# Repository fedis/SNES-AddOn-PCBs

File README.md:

SNES-AddOn-PCBs
===============

Several PCBs for SNES for Different Purposes

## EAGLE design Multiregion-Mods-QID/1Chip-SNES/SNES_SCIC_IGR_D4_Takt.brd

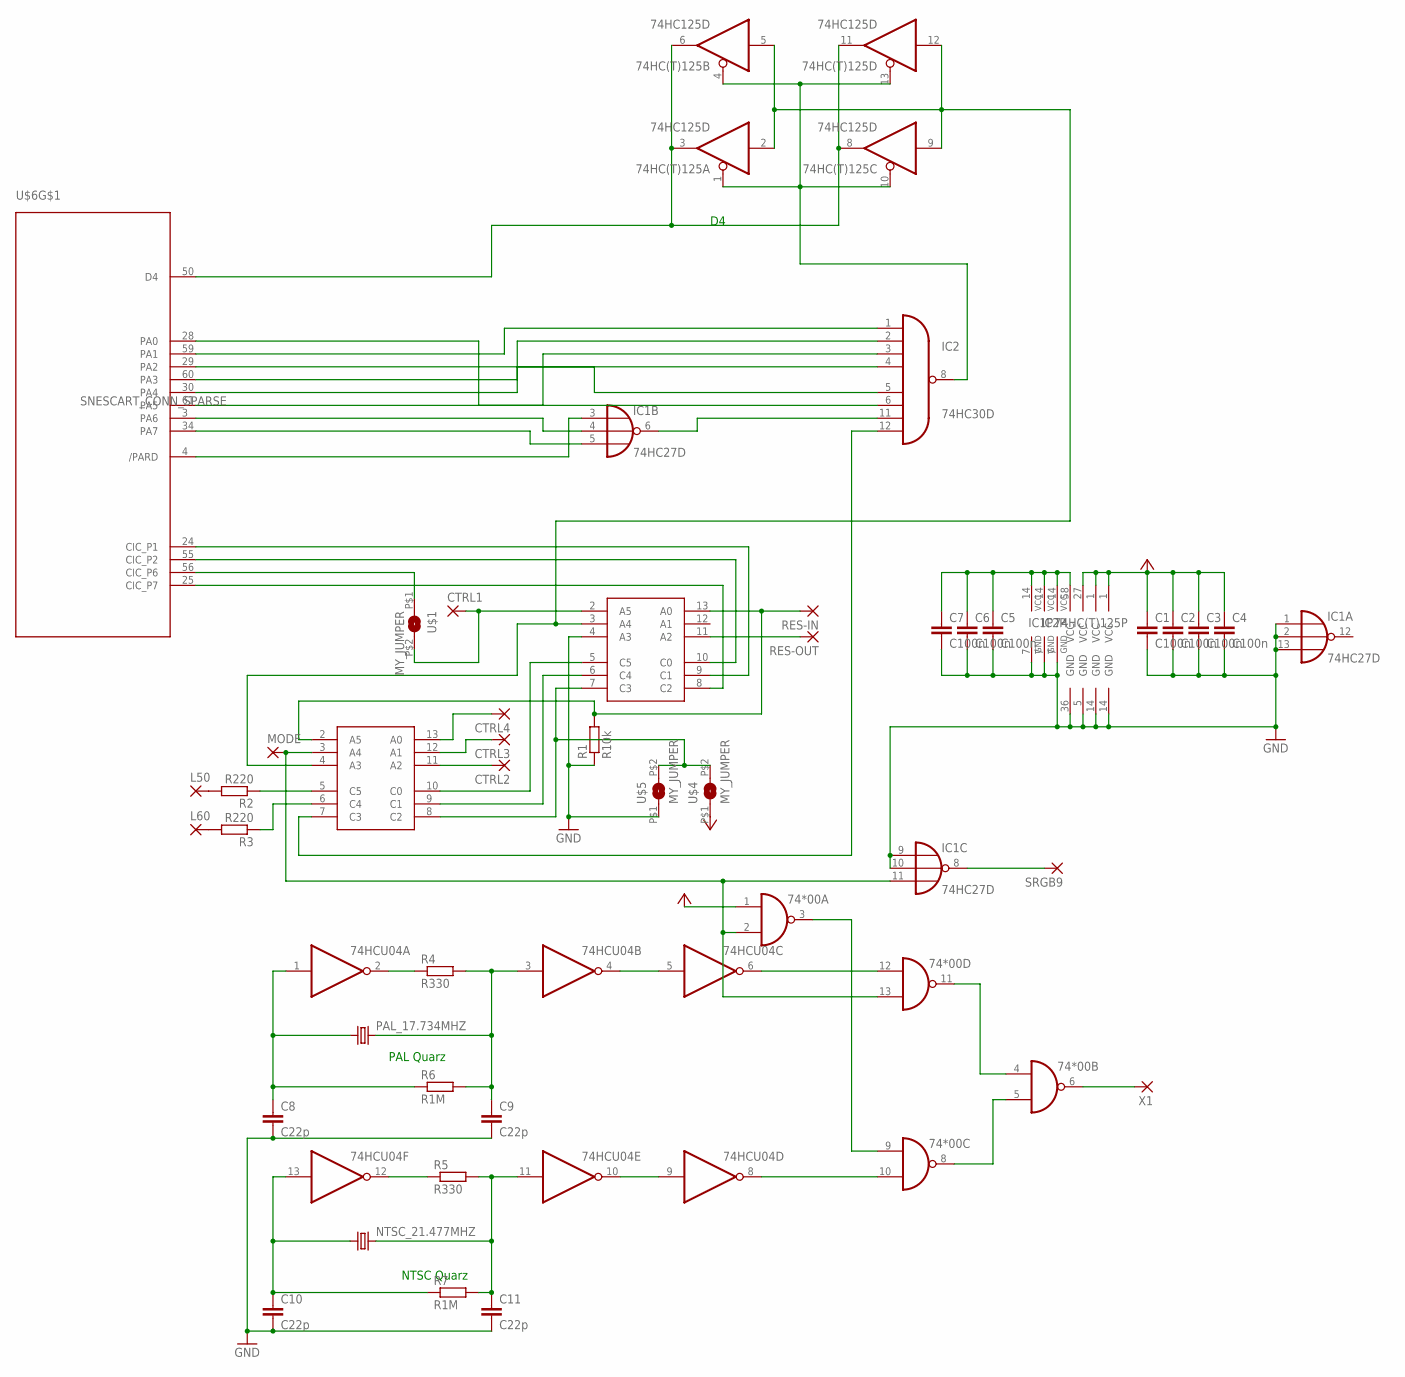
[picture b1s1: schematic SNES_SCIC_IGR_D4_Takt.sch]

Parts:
74*00: 7400D; SO14
74HC(T)125: 74HC125D; SO14
74HCU04: 74HC04D; SO14
C1, C2, C3, C4, C5, C6, C7: C100n; Z0805
C8, C9, C10, C11: C22p; Z0805
CTRL1, CTRL2, CTRL3, CTRL4: SMD2; SMD1,27-2,54
IC1: 74HC27D; SO14
IC2: 74HC30D; SO14
L50, L60: SMD2; SMD1,27-2,54
MODE: SMD2; SMD1,27-2,54
NTSC_21.477MHZ: CRYSTALHC49UP; HC49UP
PAL_17.734MHZ: CRYSTALHC49UP; HC49UP
R1: R10k; Z0805
R2, R3: R220; Z0805
R4, R5: R330; Z0805
R6, R7: R1M; Z0805
RES-IN: SMD2; SMD1,27-2,54
RES-OUT: SMD2; SMD1,27-2,54
SRGB9: SMD2; SMD1,27-2,54
U$1, U$4, U$5: MY_JUMPER; MYJUMP
U$2, U$3: PIC16F630_SIMPLE; PIC16F630
U$6: SNESCART_CONN_SPARSE
X1: SMD2; SMD1,27-2,54

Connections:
GND: 74*00.7 (GND), 74HC(T)125.7 (GND), 74HCU04.7 (GND), C1.2, C2.2, C3.2, C4.2, C5.2, C6.2, C7.2, C8.2, C9.2, C10.2, C11.2, IC1.1 (I0), IC1.2 (I1), IC1.7 (GND), IC1.9 (I0), IC1.10 (I1), IC1.13 (I2), IC2.7 (GND), R1.1, U$2.4 (A3), U$2.14 (GND), U$3.14 (GND), U$5.P$1 (1), U$6.5 (GND), U$6.36 (GND)
unnamed: IC1.8 (O), SRGB9.1
unnamed: 74HC(T)125.1 (OE), 74HC(T)125.4 (OE), 74HC(T)125.10 (OE), 74HC(T)125.13 (OE), IC2.8 (O)
unnamed: RES-OUT.1, U$2.11 (A2)
unnamed: IC2.3 (I2), U$6.61 (PA5)
unnamed: IC2.2 (I1), U$6.60 (PA3)
unnamed: IC1.3 (I0), U$6.4 (/PARD)
unnamed: IC1.4 (I1), U$6.3 (PA6)
unnamed: IC1.6 (O), IC2.11 (I6)
unnamed: IC2.6 (I5), U$6.28 (PA0)
unnamed: R1.2, RES-IN.1, U$2.13 (A0), U$3.2 (A5)
unnamed: L50.1, R2.2
unnamed: R2.1, U$3.5 (C5)
unnamed: R3.1, U$3.6 (C4)
unnamed: 74*00.2 (I1), 74*00.13 (I1), IC1.11 (I2), MODE.1, U$3.3 (A4)
unnamed: L60.1, R3.2
unnamed: IC1.5 (I2), U$6.34 (PA7)
unnamed: IC2.12 (I7), U$3.7 (C3)
unnamed: U$1.P$1 (1), U$6.56 (CIC_P6)
unnamed: U$2.5 (C5), U$3.10 (C0)
unnamed: IC2.1 (I0), U$6.59 (PA1)
unnamed: IC2.5 (I4), U$6.29 (PA2)
unnamed: IC2.4 (I3), U$6.30 (PA4)
unnamed: 74*00.12 (I0), 74HCU04.6 (O)
unnamed: 74HCU04.1 (I), C8.1, PAL_17.734MHZ.1, R6.1
unnamed: 74HCU04.3 (I), C9.1, PAL_17.734MHZ.2, R4.2, R6.2
unnamed: 74HCU04.13 (I), C10.1, NTSC_21.477MHZ.1, R7.1
unnamed: 74HCU04.11 (I), C11.1, NTSC_21.477MHZ.2, R5.2, R7.2
unnamed: 74*00.5 (I1), 74*00.8 (O)
unnamed: 74*00.4 (I0), 74*00.11 (O)
unnamed: CTRL2.1, U$3.11 (A2)
unnamed: CTRL3.1, U$3.12 (A1)
unnamed: 74*00.3 (O), 74*00.9 (I0)
unnamed: 74*00.6 (O), X1.1
unnamed: 74HCU04.2 (O), R4.1
unnamed: 74HCU04.4 (O), 74HCU04.5 (I)
unnamed: CTRL1.1, U$1.P$2 (2), U$2.2 (A5)
unnamed: 74*00.10 (I1), 74HCU04.8 (O)
unnamed: 74HC(T)125.3 (O), 74HC(T)125.6 (O), 74HC(T)125.8 (O), 74HC(T)125.11 (O), U$6.50 (D4)
unnamed: 74HCU04.9 (I), 74HCU04.10 (O)
unnamed: CTRL4.1, U$3.13 (A0)
unnamed: U$2.10 (C0), U$6.55 (CIC_P2)
unnamed: U$2.9 (C1), U$6.24 (CIC_P1)
unnamed: 74HCU04.12 (O), R5.1
unnamed: U$2.8 (C2), U$6.25 (CIC_P7)
unnamed: U$2.6 (C4), U$3.9 (C1)
unnamed: U$2.7 (C3), U$3.8 (C2), U$4.P$2 (2), U$5.P$2 (2)
UIGR: 74HC(T)125.2 (I), 74HC(T)125.5 (I), 74HC(T)125.9 (I), 74HC(T)125.12 (I), U$2.3 (A4), U$3.4 (A3)
VCC: 74*00.1 (I0), 74*00.14 (VCC), 74HCU04.14 (VCC), C1.1, C2.1, C3.1, C4.1, U$2.1 (VCC), U$3.1 (VCC), U$4.P$1 (1), U$6.27 (VCC)
VCC_2: 74HC(T)125.14 (VCC), C5.1, C6.1, C7.1, IC1.14 (VCC), IC2.14 (VCC), U$6.58 (VCC)

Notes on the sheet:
PAL Quarz
NTSC Quarz

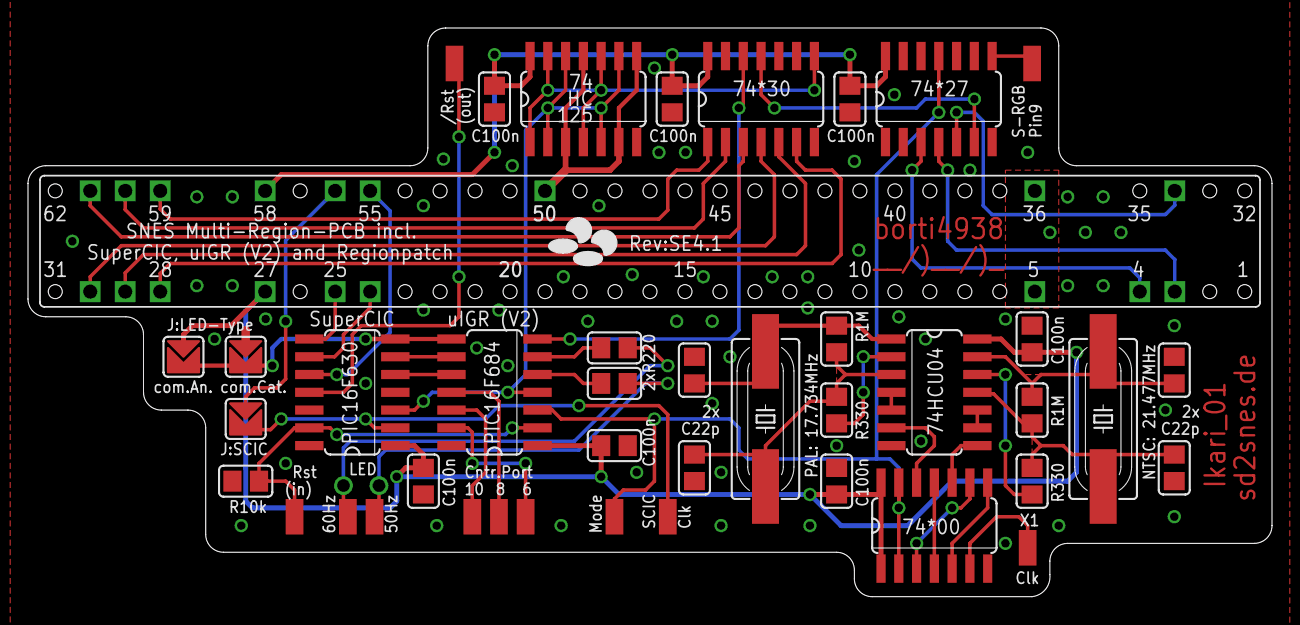
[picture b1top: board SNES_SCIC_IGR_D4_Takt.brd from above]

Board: 2 copper layers, 88.9 x 40.6 mm, 42 parts (0 on the bottom side), 50 nets.

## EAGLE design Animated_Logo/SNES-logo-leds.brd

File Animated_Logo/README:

Installation
=============

The PCB is designed to be assembled to the extension port of the ‘normal’ SNES.
/Rst is a combination of a pad and a jumper, which can be used as follows:
– connect the pad with a wire to CIC pad 10 (animation is repeated on a reset using reset button and the IGR (PIC-microcontroller code)
– close jumper: animation is repeated on every reset (I do not like this, e.g., because the sd2snes performs a reset on startup and the animation is started a second time while the initial animation is running)
– neither connect the wire or the close the jumper: animation is just played once

Others:
=======

- Software: http://circuit-board.de/forum/index.php/Thread/7573-Super-Nintendo-Beleuchtetes-animiertes-Logo/
- Fuse Bits for the ATTiny45: lfuse: 0xe2, hfuse:w:0xdf
- The given resistor values for the LEDs (2x 150Ohm (yellow, red) and 2x 100Ohm (green, blue)) are just examples. You may adjust these values according to your needs :)
- LEDs are in 0805 package.

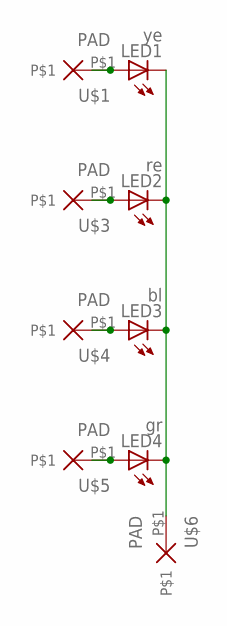
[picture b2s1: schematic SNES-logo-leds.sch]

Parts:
LED1: ye; SML0805
LED2: re; SML0805
LED3: bl; SML0805
LED4: gr; SML0805
U$1, U$3, U$4, U$5, U$6: PAD

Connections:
unnamed: LED1.C, LED2.C, LED3.C, LED4.C, U$6.P$1
unnamed: LED1.A, U$1.P$1
unnamed: LED2.A, U$3.P$1
unnamed: LED3.A, U$4.P$1
unnamed: LED4.A, U$5.P$1

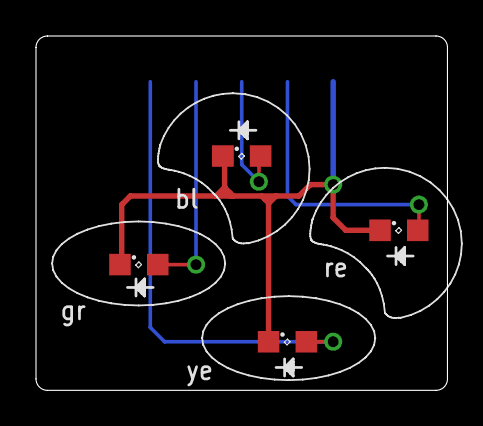
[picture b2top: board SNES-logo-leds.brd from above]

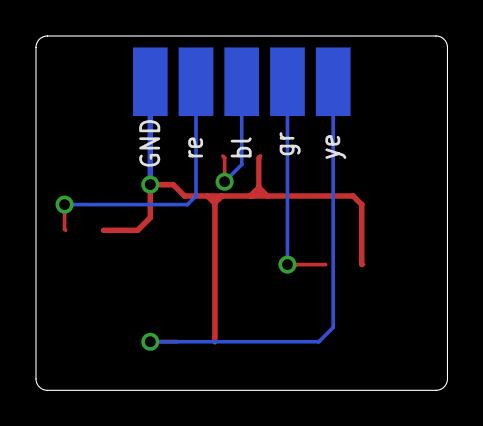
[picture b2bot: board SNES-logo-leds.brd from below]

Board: 2 copper layers, 22.9 x 19.7 mm, 9 parts (5 on the bottom side), 5 nets.

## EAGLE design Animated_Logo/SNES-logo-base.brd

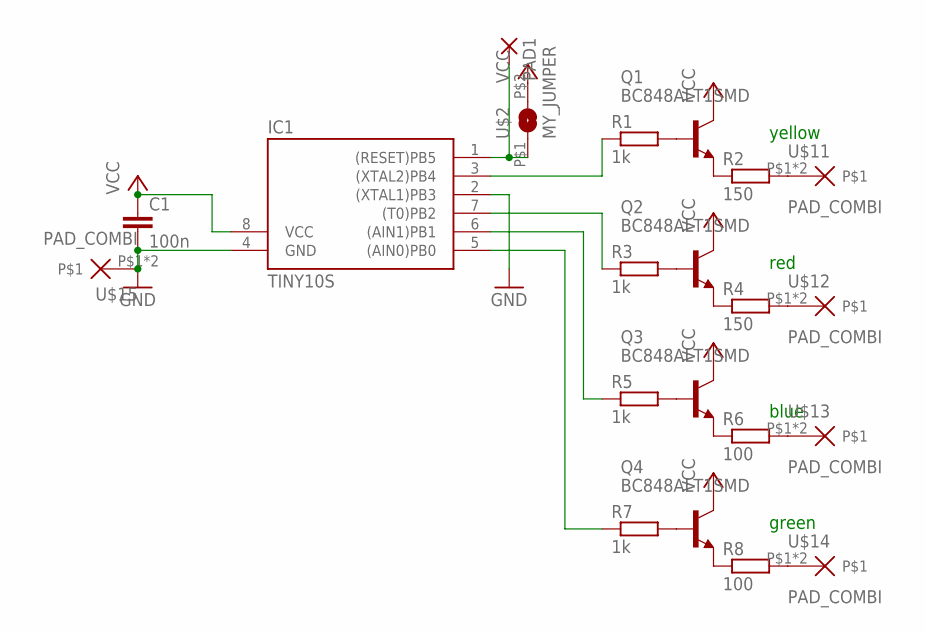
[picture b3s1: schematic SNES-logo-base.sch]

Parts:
C1: 100n; Z0805
IC1: TINY10S; SOIC8
PAD1: SMD2; SMD1,27-2,54
Q1, Q2, Q3, Q4: BC848ALT1SMD; SOT23
R1, R3, R5, R7: 1k; Z0805
R2, R4: 150; Z0805
R6, R8: 100; Z0805
U$2: MY_JUMPER; MYJUMP
U$11, U$12, U$13, U$14, U$15: PAD_COMBI

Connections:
GND: C1.2, IC1.2 ((XTAL1)PB3), IC1.4 (GND), U$15.P$1, U$15.P$2
unnamed: IC1.1 ((RESET)PB5), PAD1.1, U$2.P$1 (1)
unnamed: Q1.1 (B), R1.2
unnamed: Q2.1 (B), R3.2
unnamed: Q3.1 (B), R5.2
unnamed: Q4.1 (B), R7.2
unnamed: Q1.2 (E), R2.1
unnamed: Q2.2 (E), R4.1
unnamed: Q3.2 (E), R6.1
unnamed: Q4.2 (E), R8.1
unnamed: IC1.3 ((XTAL2)PB4), R1.1
unnamed: IC1.7 ((T0)PB2), R3.1
unnamed: IC1.6 ((AIN1)PB1), R5.1
unnamed: IC1.5 ((AIN0)PB0), R7.1
unnamed: R2.2, U$11.P$1, U$11.P$2
unnamed: R4.2, U$12.P$1, U$12.P$2
unnamed: R6.2, U$13.P$1, U$13.P$2
unnamed: R8.2, U$14.P$1, U$14.P$2
VCC: C1.1, IC1.8 (VCC), Q1.3 (C), Q2.3 (C), Q3.3 (C), Q4.3 (C), U$2.P$2 (2)

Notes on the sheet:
yellow
red
blue
green

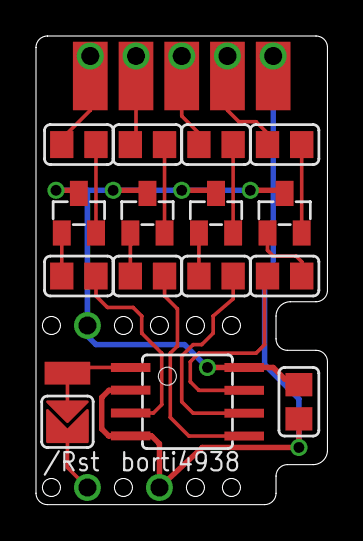
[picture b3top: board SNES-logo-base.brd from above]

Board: 2 copper layers, 16.2 x 26.0 mm, 21 parts (0 on the bottom side), 19 nets.

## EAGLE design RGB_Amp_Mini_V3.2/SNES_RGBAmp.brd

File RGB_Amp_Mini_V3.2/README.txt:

Solder Joints:

  R - red image component from S-CPUN pin156
  G - green image component from S-CPUN pin157
  B - blue image component from S-CPUN pin158

solder PCB directly beneath the MultiAV
deactivate the RGB-output of S-RGB by lifting pin20, 22 and 24 from mainboard

equivalent installation guides: http://www.retrorgb.com/1chiprgb.html
(with this version, there is no need to adjust any brightness issues ;) It is done on the PCB with R7 — R12)

After modding there is no need for any components within the RGB-lines in the RGB cable. However, you may modify the board to use standard cables (see notes in brackets).

-----------------------------------------------------------------------------------

Values of passive components (0805 packages):

 R1 -  R3: 75 Ohm (0805 packages)
 R4 -  R6: 75 Ohm (0805 packages, only iff you use standard PAL-RGB cable)
 R7 -  R9: 750 Ohm (0805 packages, these are the three resistors next to the THS7314)
R10 - R12: 7.5 kOhm (0805 packages, these are the three resistors at the outer left of the PCB)
 C1       : 0.1uF (0805 package)
 C2       : 22uF ratet with >6.3V (tantal type C)
 C3 - C5  : 330uF ratet with >6.3V (tantal type D; just short the places if you use a standard NTSC-RGB cable)

-----------------------------------------------------------------------------------

Active IC (SOIC8 packages):

THS7314: for more information see ti.com (THS7316 is also applicable to use)

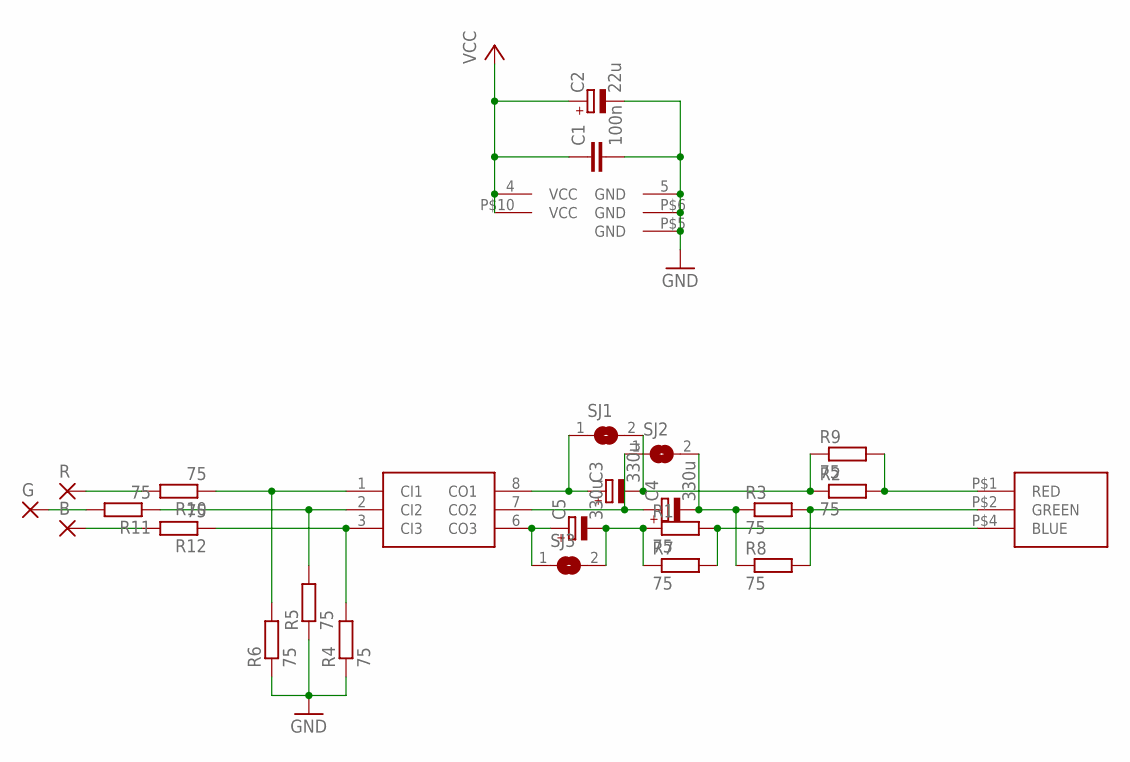
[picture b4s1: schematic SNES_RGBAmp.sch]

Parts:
B: SMD2; SMD1,27-2,54
C1: 100n; Z0805
C2: 22u; SMC_C
C3, C4, C5: 330u; SMC_D
G: SMD2; SMD1,27-2,54
R: SMD2; SMD1,27-2,54
R1, R2, R3, R4, R5, R6, R7, R8, R9, R10, R11, R12: 75; Z0805
SJ1, SJ2, SJ3: SJ
U$1: THS7314
U$2: SNES_MULTIAV_RGB_ONLY

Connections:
GND: C1.2, C2.-, R4.1, R5.1, R6.1, U$1.5 (GND), U$2.P$5 (GND), U$2.P$6 (GND)
unnamed: R6.2, R10.1, U$1.1 (CI1)
unnamed: R5.2, R11.1, U$1.2 (CI2)
unnamed: R4.2, R12.1, U$1.3 (CI3)
unnamed: C3.-, R2.1, R9.1, SJ1.2
unnamed: R2.2, R9.2, U$2.P$1 (RED)
unnamed: R3.2, R8.2, U$2.P$2 (GREEN)
unnamed: C4.+, SJ2.1, U$1.7 (CO2)
unnamed: C5.-, R1.1, R7.1, SJ3.2
unnamed: R1.2, R7.2, U$2.P$4 (BLUE)
unnamed: C5.+, SJ3.1, U$1.6 (CO3)
unnamed: C3.+, SJ1.1, U$1.8 (CO1)
unnamed: C4.-, R3.1, R8.1, SJ2.2
unnamed: R.1, R10.2
unnamed: G.1, R11.2
unnamed: B.1, R12.2
VCC: C1.1, C2.+, U$1.4 (VCC), U$2.P$10 (VCC)

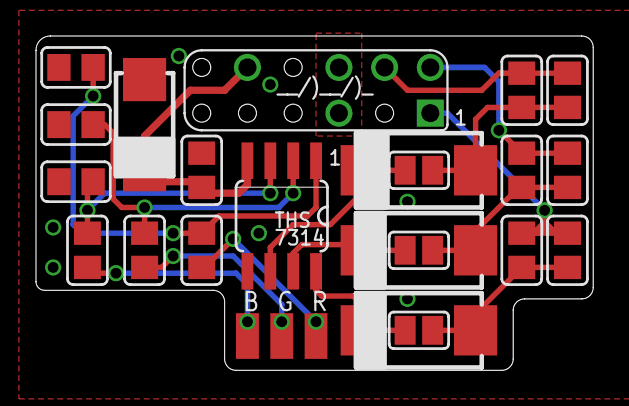
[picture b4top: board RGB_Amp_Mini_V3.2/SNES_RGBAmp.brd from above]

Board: 2 copper layers, 31.0 x 18.6 mm, 25 parts (0 on the bottom side), 17 nets.

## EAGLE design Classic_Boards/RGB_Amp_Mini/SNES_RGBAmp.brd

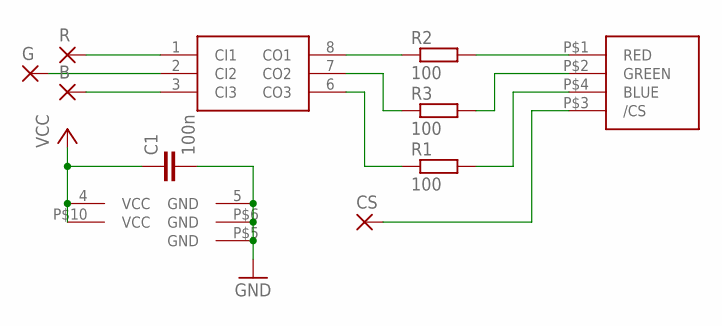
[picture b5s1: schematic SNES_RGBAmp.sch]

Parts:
B: SMD2; SMD1,27-2,54
C1: 100n; Z0805
CS: SMD2; SMD1,27-2,54
G: SMD2; SMD1,27-2,54
R: SMD2; SMD1,27-2,54
R1, R2, R3: 100; Z0805
U$1: THS7314
U$3: SNES_MULTIAV_RGBC_ONLY

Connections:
GND: C1.2, U$1.5 (GND), U$3.P$5 (GND), U$3.P$6 (GND)
unnamed: R.1, U$1.1 (CI1)
unnamed: G.1, U$1.2 (CI2)
unnamed: B.1, U$1.3 (CI3)
unnamed: R2.1, U$1.8 (CO1)
unnamed: R2.2, U$3.P$1 (RED)
unnamed: R3.2, U$3.P$2 (GREEN)
unnamed: R3.1, U$1.7 (CO2)
unnamed: R1.1, U$1.6 (CO3)
unnamed: R1.2, U$3.P$4 (BLUE)
unnamed: CS.1, U$3.P$3 (/CS)
VCC: C1.1, U$1.4 (VCC), U$3.P$10 (VCC)

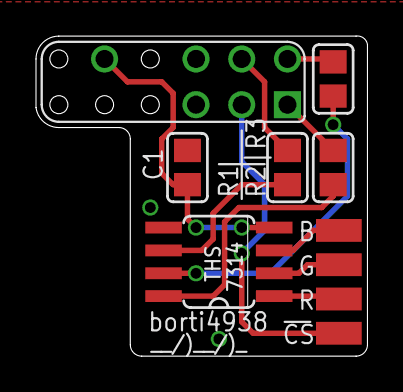
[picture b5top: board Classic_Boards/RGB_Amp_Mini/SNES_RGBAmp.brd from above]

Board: 2 copper layers, 18.4 x 17.8 mm, 10 parts (0 on the bottom side), 12 nets.

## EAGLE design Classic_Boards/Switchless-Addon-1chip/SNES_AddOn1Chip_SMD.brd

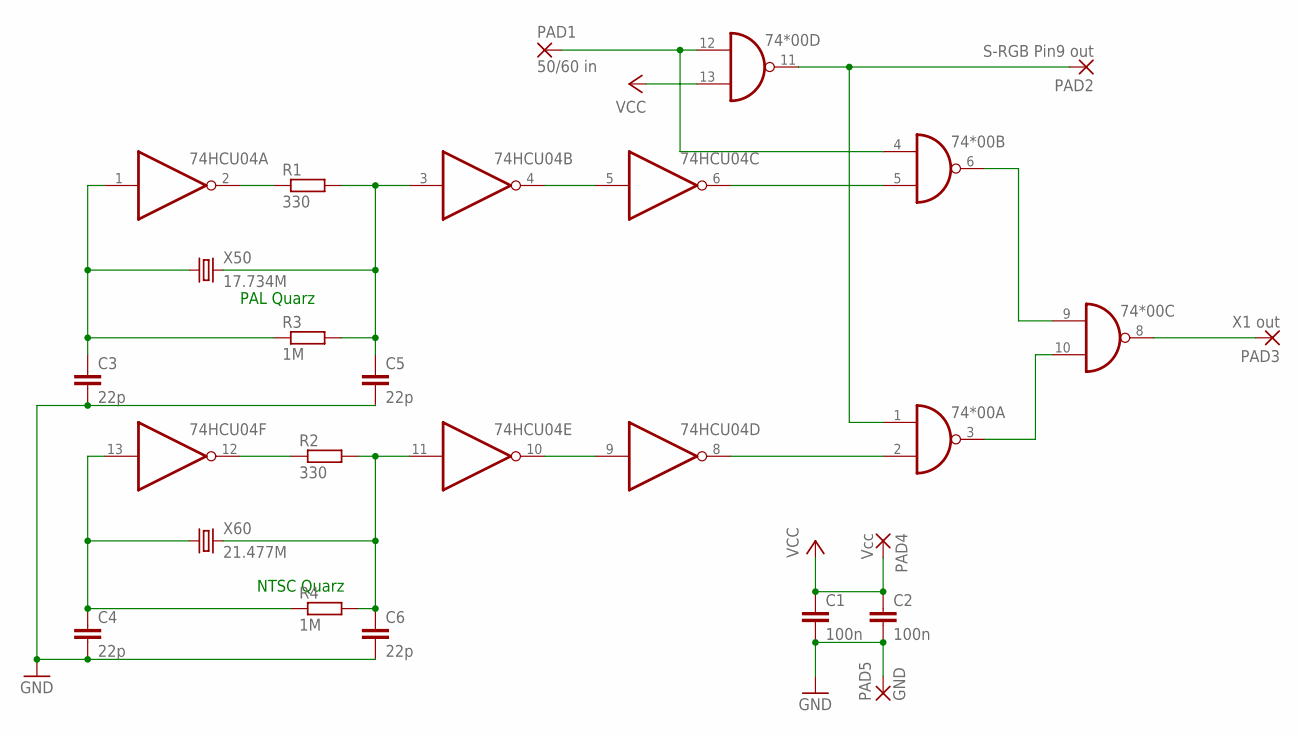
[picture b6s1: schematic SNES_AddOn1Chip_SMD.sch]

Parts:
74*00: 7400D; SO14
74HCU04: 74HC04D; SO14
C1, C2: 100n; Z0805
C3, C4, C5, C6: 22p; Z0805
PAD1: 50/60 in; SMD1,27-2,54
PAD2: S-RGB Pin9 out; SMD1,27-2,54
PAD3: X1 out; SMD1,27-2,54
PAD4: Vcc; SMD2,54-5,08
PAD5: GND; SMD2,54-5,08
R1, R2: 330; Z0805
R3, R4: 1M; Z0805
X50: 17.734M; MY_SMD_CRYSTAL2
X60: 21.477M; MY_SMD_CRYSTAL2

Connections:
GND: 74*00.7 (GND), 74HCU04.7 (GND), C1.2, C2.2, C3.2, C4.2, C5.2, C6.2, PAD5.1
unnamed: 74HCU04.1 (I), C3.1, R3.1, X50.1
unnamed: 74HCU04.3 (I), C5.1, R1.2, R3.2, X50.2
unnamed: 74HCU04.13 (I), C4.1, R4.1, X60.1
unnamed: 74HCU04.11 (I), C6.1, R2.2, R4.2, X60.2
unnamed: 74*00.3 (O), 74*00.10 (I1)
unnamed: 74*00.6 (O), 74*00.9 (I0)
unnamed: 74*00.4 (I0), 74*00.12 (I0), PAD1.1
unnamed: 74*00.1 (I0), 74*00.11 (O), PAD2.1
unnamed: 74*00.8 (O), PAD3.1
unnamed: 74HCU04.2 (O), R1.1
unnamed: 74HCU04.4 (O), 74HCU04.5 (I)
unnamed: 74*00.5 (I1), 74HCU04.6 (O)
unnamed: 74*00.2 (I1), 74HCU04.8 (O)
unnamed: 74HCU04.9 (I), 74HCU04.10 (O)
unnamed: 74HCU04.12 (O), R2.1
VCC: 74*00.13 (I1), 74*00.14 (VCC), 74HCU04.14 (VCC), C1.1, C2.1, PAD4.1

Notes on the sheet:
PAL Quarz
NTSC Quarz

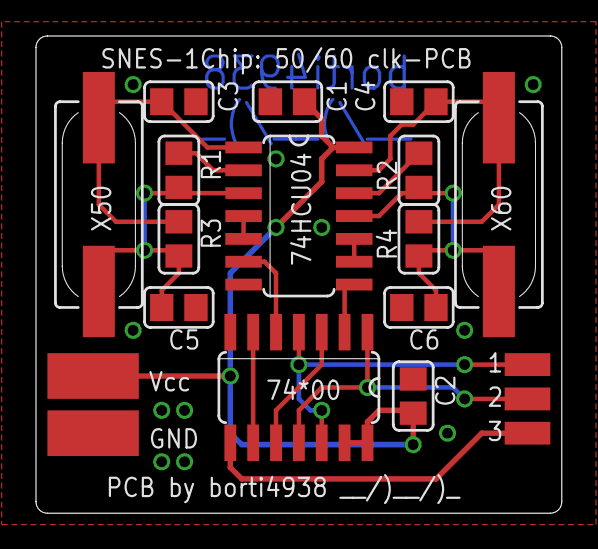
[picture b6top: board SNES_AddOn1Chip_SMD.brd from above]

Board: 2 copper layers, 29.2 x 26.5 mm, 19 parts (0 on the bottom side), 17 nets.

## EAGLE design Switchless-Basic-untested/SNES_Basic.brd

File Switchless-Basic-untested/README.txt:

!!! THIS IS AN UNTESTED VERSION OF THE PCB!!!

The aim of the new version is to get rid of the 74*133 of the previous version, because the 74*133 is hard to find or very expensive...

Solder Joints:

- Most of the solder joints are located at the cart connector as to be seen
on the silkscreen.
- The mode output located at the PCBs bottom right side is goin' to the
  - S-CPUN Pin 111
  - S-PPU1 Pin 24 and S-PPU2 Pin 30
  - One may use the additional pad for the add-on PCB for the 1Chip-SNES or
  to use separate wires to S-PPU1 and S-PPU2
- CIC8 and CIC10 has to be solder to the pads, not the the lifted pins
  - Reset input can be solder direktly to the reset buttons output instead of CIC8
- 'Contr. Port' means the connector for the flat wire. In the SNES-mini the mapping
is as follows:
  - 10 -> Player1 Pin3
  -  8 -> Player1 Pin2
  -  6 -> Player1 Pin4

-----------------------------------------------------------------------------------
Lifted Pins:

- S-CPUN Pin 111 OR S-PPU1 Pin 24 and S-PPU2 Pin 30
- CIC Pins 1, 2, 10 and 11 OR remove CIC completely

-----------------------------------------------------------------------------------

Values of passive components (all 0805 packages except crystals):

R1, R2: 220Ohm (increase resistor values if LED is too bright)
C1 - C5: 0.1uF

-----------------------------------------------------------------------------------

Active ICs (SOIC14 packages):

74*27: three 3-NOR gates, where two are unused
74HC(T)125: four buffer gate: use HC or HCT type!
74*30: 8-NAND gate

S-CIC: PIC16F630 flashed with 'Firmware_SCIC.hex' or 'supercic-lock.hex' (sd2snes-repo)
uIGR (V2): PIC16F684 flashed with 'Firmware_uIGR_V2.hex' or 'snes-uigr.hex' (sd2snes-repo)
!!!Note that the 'snes-igr.hex' in the sd2snes repository, i.e., the 'classical igr' won't work
on this PCB!!!

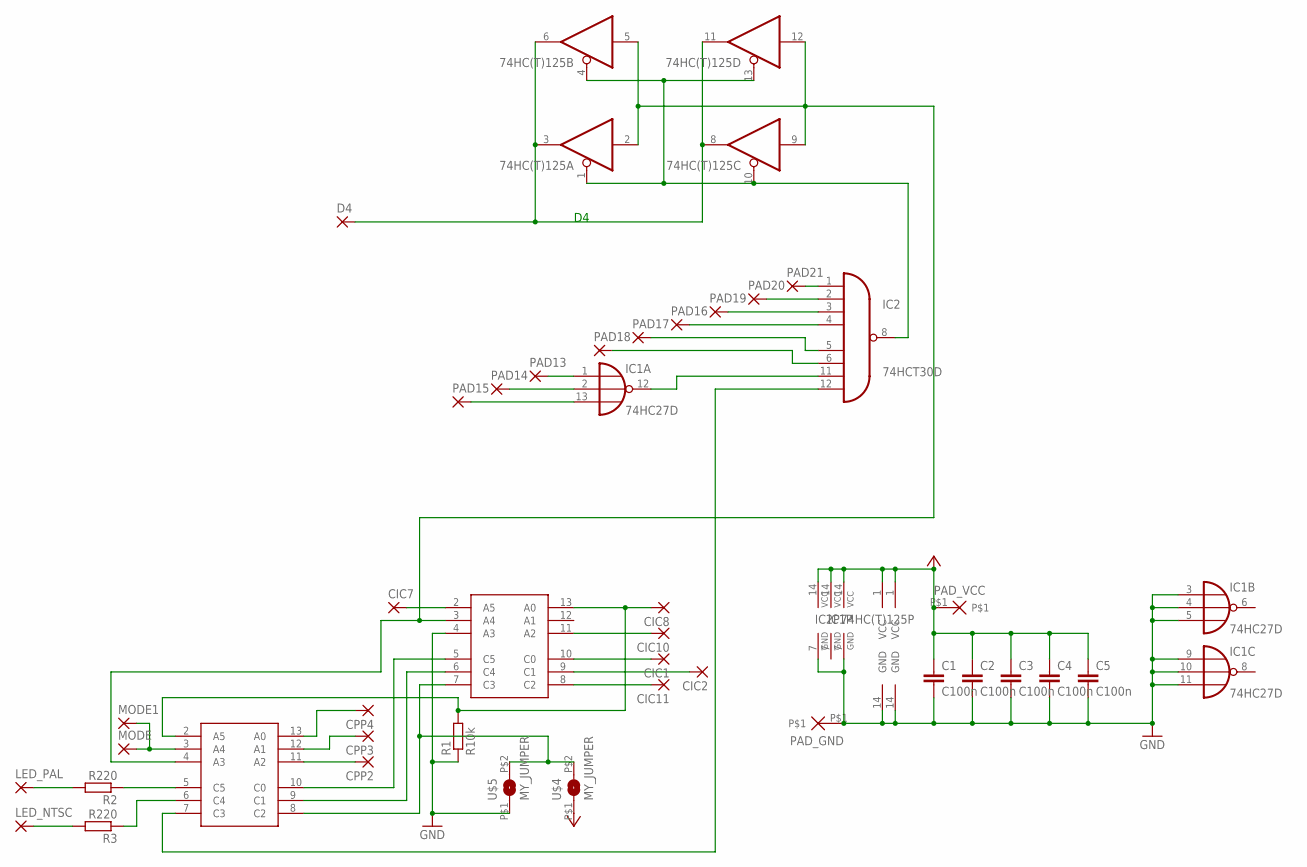
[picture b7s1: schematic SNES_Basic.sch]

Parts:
74HC(T)125: 74HCT125D; SO14
C1, C2, C3, C4, C5: C100n; Z0805
CIC1, CIC2, CIC7, CIC8, CIC10, CIC11: SMD2; SMD1,27-2,54
CPP2, CPP3, CPP4: SMD2; SMD1,27-2,54
D4: SMD2; SMD1,27-2,54
IC1: 74HC27D; SO14
IC2: 74HCT30D; SO14
LED_NTSC: SMD2; SMD1,27-2,54
LED_PAL: SMD2; SMD1,27-2,54
MODE, MODE1: SMD2; SMD1,27-2,54
PAD13, PAD14, PAD15, PAD16, PAD17, PAD18, PAD19, PAD20, PAD21: SMD2; SMD1,27-2,54
PAD_GND: PAD; PADS
PAD_VCC: PAD; PADS
R1: R10k; Z0805
R2, R3: R220; Z0805
U$2, U$3: PIC16F630_SIMPLE; PIC16F630
U$4, U$5: MY_JUMPER; MYJUMP

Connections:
D4_ON/OFF: IC2.12 (I7), U$3.7 (C3)
GND: 74HC(T)125.7 (GND), C1.2, C2.2, C3.2, C4.2, C5.2, IC1.3 (I0), IC1.4 (I1), IC1.5 (I2), IC1.7 (GND), IC1.9 (I0), IC1.10 (I1), IC1.11 (I2), IC2.7 (GND), PAD_GND.P$1, R1.1, U$2.4 (A3), U$2.14 (GND), U$3.14 (GND), U$5.P$1 (1)
unnamed: LED_PAL.1, R2.2
unnamed: 74HC(T)125.1 (OE), 74HC(T)125.4 (OE), 74HC(T)125.10 (OE), 74HC(T)125.13 (OE), IC2.8 (O)
unnamed: CIC10.1, U$2.11 (A2)
unnamed: IC2.5 (I4), PAD17.1
unnamed: IC2.4 (I3), PAD16.1
unnamed: IC2.3 (I2), PAD19.1
unnamed: IC2.2 (I1), PAD20.1
unnamed: IC2.1 (I0), PAD21.1
unnamed: CIC7.1, U$2.2 (A5)
unnamed: CIC8.1, R1.2, U$2.13 (A0), U$3.2 (A5)
unnamed: IC1.1 (I0), PAD13.1
unnamed: R2.1, U$3.5 (C5)
unnamed: R3.1, U$3.6 (C4)
unnamed: LED_NTSC.1, R3.2
unnamed: IC2.6 (I5), PAD18.1
unnamed: IC1.12 (O), IC2.11 (I6)
unnamed: IC1.13 (I2), PAD15.1
unnamed: U$2.5 (C5), U$3.10 (C0)
unnamed: IC1.2 (I1), PAD14.1
unnamed: CPP2.1, U$3.11 (A2)
unnamed: CPP3.1, U$3.12 (A1)
unnamed: 74HC(T)125.3 (O), 74HC(T)125.6 (O), 74HC(T)125.8 (O), 74HC(T)125.11 (O), D4.1
unnamed: CPP4.1, U$3.13 (A0)
unnamed: CIC1.1, U$2.10 (C0)
unnamed: CIC2.1, U$2.9 (C1)
unnamed: CIC11.1, U$2.8 (C2)
unnamed: U$2.6 (C4), U$3.9 (C1)
unnamed: U$2.7 (C3), U$3.8 (C2), U$4.P$2 (2), U$5.P$2 (2)
unnamed: MODE.1, MODE1.1, U$3.3 (A4)
UIGR: 74HC(T)125.2 (I), 74HC(T)125.5 (I), 74HC(T)125.9 (I), 74HC(T)125.12 (I), U$2.3 (A4), U$3.4 (A3)
VCC: 74HC(T)125.14 (VCC), C1.1, C2.1, C3.1, C4.1, C5.1, IC1.14 (VCC), IC2.14 (VCC), PAD_VCC.P$1, U$2.1 (VCC), U$3.1 (VCC), U$4.P$1 (1)

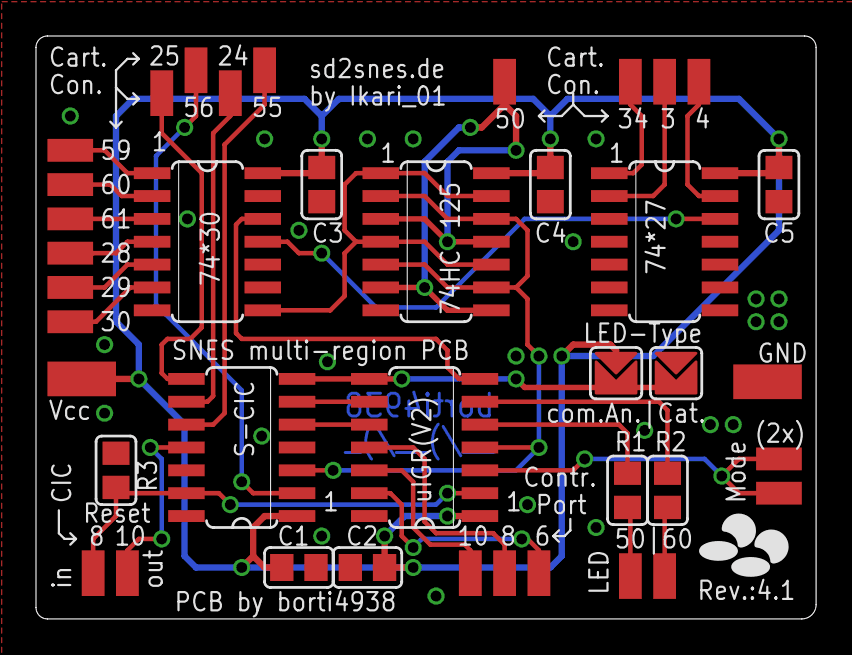
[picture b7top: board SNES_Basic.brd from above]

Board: 2 copper layers, 43.3 x 32.4 mm, 40 parts (0 on the bottom side), 33 nets.

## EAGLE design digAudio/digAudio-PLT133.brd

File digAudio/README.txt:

Solder Joints:

A mapping Pads of PCB to S-DSP/S-APU is given on the bottoms silkscreen

-----------------------------------------------------------------------------------

Values of passive components (all 0805 packages):

C1 - C3: 0.1uF

-----------------------------------------------------------------------------------

Active ICs (SOIC28 package):

CS8406-CSZ

-----------------------------------------------------------------------------------

Audio Output:

Optical SPDIF - Everlight IR-Fotolink 3-5V Plt131

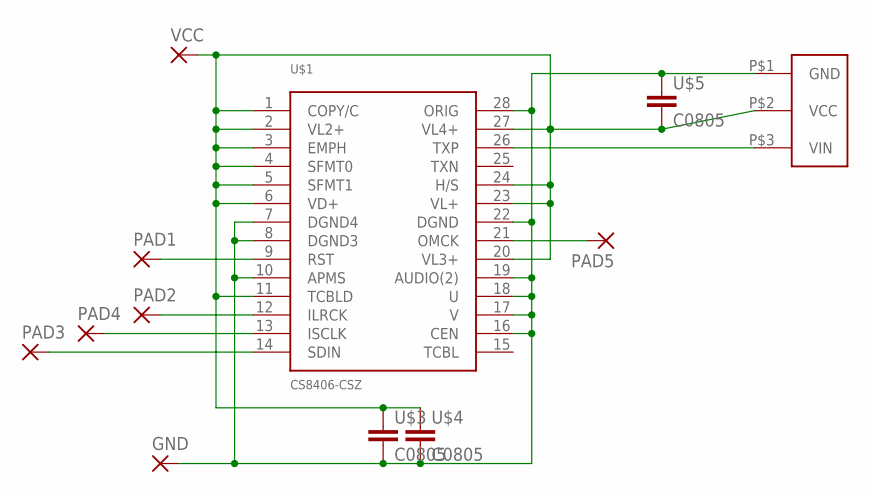
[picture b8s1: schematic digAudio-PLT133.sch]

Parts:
GND: SMD2; SMD1,27-2,54
PAD1, PAD2, PAD3, PAD4, PAD5: SMD2; SMD1,27-2,54
U$1: CS8406-CSZ; SO28W
U$3, U$4, U$5: C0805; Z0805
U$6: PLT133/T10W
VCC: SMD2; SMD1,27-2,54

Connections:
GND: GND.1, U$1.7 (DGND4), U$1.8 (DGND3), U$1.10 (APMS), U$1.16 (CEN), U$1.17 (V), U$1.18 (U), U$1.19 (AUDIO(2)), U$1.22 (DGND), U$1.28 (ORIG), U$3.2, U$4.2, U$5.1, U$6.P$1 (GND)
unnamed: U$1.26 (TXP), U$6.P$3 (VIN)
unnamed: PAD1.1, U$1.9 (RST)
unnamed: PAD2.1, U$1.12 (ILRCK)
unnamed: PAD4.1, U$1.13 (ISCLK)
unnamed: PAD3.1, U$1.14 (SDIN)
unnamed: PAD5.1, U$1.21 (OMCK)
VCC: U$1.1 (COPY/C), U$1.2 (VL2+), U$1.3 (EMPH), U$1.4 (SFMT0), U$1.5 (SFMT1), U$1.6 (VD+), U$1.11 (TCBLD), U$1.20 (VL3+), U$1.23 (VL+), U$1.24 (H/S), U$1.27 (VL4+), U$3.1, U$4.1, U$5.2, U$6.P$2 (VCC), VCC.1

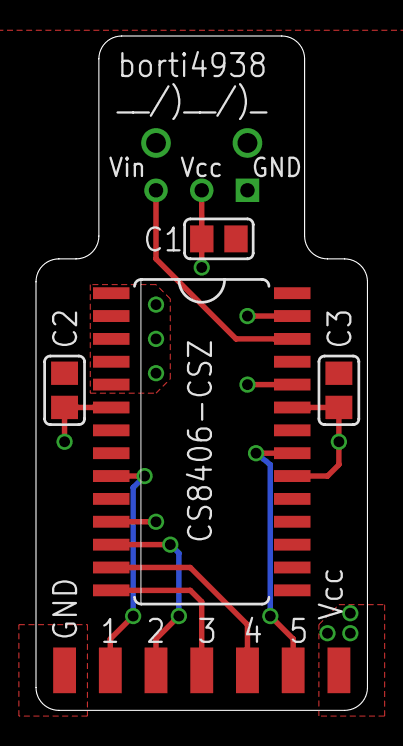
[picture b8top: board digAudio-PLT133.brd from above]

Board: 2 copper layers, 18.4 x 37.5 mm, 12 parts (1 on the bottom side), 8 nets.

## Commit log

2014-05-30 several Libs (quite nasty sorted)
2014-05-30 RGB-Amp-PCB using THS7314/7316 to solder beneath the MultiAV (SNS-CPU-1Chip-01/02)
2014-05-30 RGB-Amp-PCB using THS7314/7316 to solder beneath the MultiAV (SNS-CPU-1Chip-03 and SNES-Mini/Jr.)
2014-05-30 Add-On-PCB for PAL/NTSC-mode switching at S-CPUN (SuperCIC/IGR-mode in 1Chip-SNES)
2014-05-30 Adapter-PCB for digital audio mod with CS8406 and optical output
2014-05-30 Add values of passive components to README
2014-05-31 Add more details in readme
2014-05-31 Add readme
2014-05-31 revert mistakes
2014-06-19 Just a few Updates
2014-06-19 Add README.txt
2014-06-29 Add Firmware for PICs actually used
2014-06-29 Last version of the official all-in-one PCB for the communities: - Circuit-Board, - SNES-Forum and - snesfreaks
2014-06-29 Basic switchless PCB for SNES incl. SuperCIC, uIGR V2 and internal region patching
2014-07-29 Replace unused solder points at the MultiAV by simple holes
2014-07-29 Add simplified MultiAVs for small RGBamp-PCBs
2014-07-29 Minor Changes - nothing to mention
2014-07-29 correct two silkscreen errors
2014-07-29 Add new uIGR firmware (beta)
2014-07-31 Small typo correction, add description for beta Firmware (uIGR)
2014-10-21 Add last Firmware for uIGR, Remove old one -> new one is compatible to games not using the AJR
2014-10-21 Add manuals in PDF (without lock)
2014-10-28 minor update (removing nops in corresponding *.asm)
2014-12-01 Improve Performance (especially in SCIC- and Auto-mode) - see sd2snes repo for more details (commit d7def973e1a61bafcf04953e68500a9e5679ad49)
2015-01-07 Update silkscreen
2015-01-07 Update DRC to meet OSH Park instead of Itead
2015-01-07 Clock switch with crystals in SMD
2015-01-07 Update PCBs incl. the DRC and add a new version with an optical jack available at digikey
2015-01-07 update libs
2015-01-07 test a new regionpatching format as the 74HC133 is hardly to find everything else stayed the same as on the other design
2015-05-05 Create a new structure… … to upload the quick-installation-designs (QID) as well as improved designs
2015-05-05 Add .gitignore
2015-05-05 Add multi region mod PCB as quick-installation-design (QID) The PCBs include SuperCIC, uIGR and region patching as well as an electronic clock switch for SNESes with S-CPUN.
2015-05-05 Add a RGB-bypass PCB with improved structure This PCB allows you to have correct color brightness at the output. This design should be universal ;)
2015-05-05 Add a picture of the QID boards
2015-05-08 Minor Update (routing of wires from SuperCIC to cart.slot)
2015-05-08 Add the animated logo (parts are noted on the silkscreen)
2015-05-08 Highlight supporters on top layer
2015-05-11 Add installation guide: QID-PCBs for multi-region SNES
